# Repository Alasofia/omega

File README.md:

# Omega

Hot swap

Solder

Omega4

The omega is a hot swap 30%(30 or 29 keys depending on the layout you choose) inspired by the [Zlant](https://www.reddit.com/r/MechanicalKeyboards/search?q=zlant&restrict_sr=1) and the [Alpha 28](https://geekhack.org/index.php?topic=99040.0) keyboards.  
The omeaga4 adds a 4th with a few options to make this more than a novelty piece.

The plate files, stls for 3D printing, and STEP files can be found in the [docs](./docs) folder.  
There are also gerbers already generated in the gerber folders.

This version was modified by Alas for LuTang.
The spacebar options were replaced with 2x2u.

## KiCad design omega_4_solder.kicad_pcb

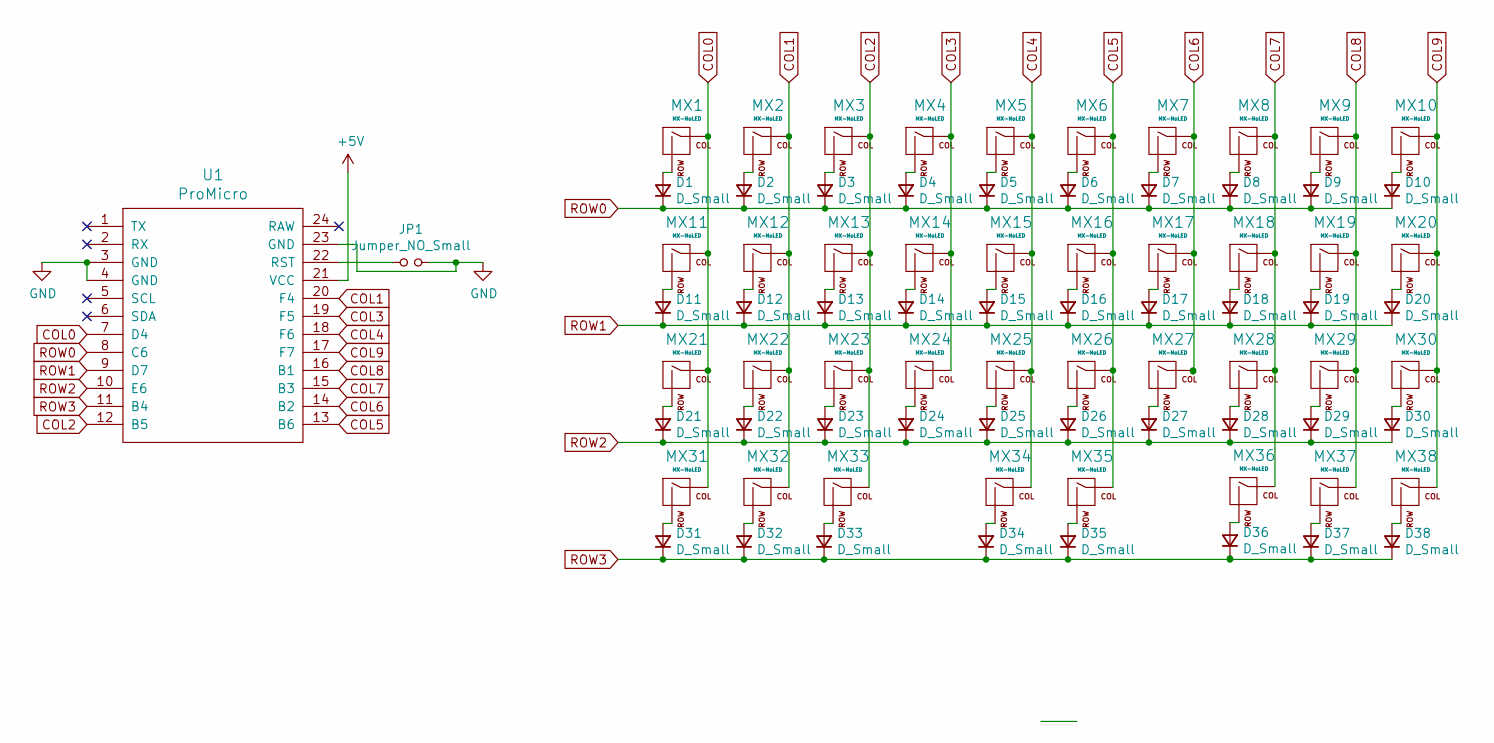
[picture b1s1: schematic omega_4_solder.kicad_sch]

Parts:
D1, D2, D3, D4, D5, D6, D7, D8, D9, D10, D11, D12, D13, D14, D15, D16, D17, D18, D19, D20, D21, D22, D23, D24, D25, D26, D27, D28, D29, D30, D31, D32, D33, D34, D35, D36, D37, D38: D_Small; Diode-Hybrid-Back
JP1: Jumper_NO_Small; Jumper-UserFriendly-Small
MX1, MX2, MX3, MX4, MX5, MX6, MX7, MX8, MX9, MX10, MX11, MX12, MX13, MX14, MX15, MX16, MX17, MX18, MX19, MX20, MX21, MX22, MX23, MX24, MX25, MX26, MX27, MX28, MX29, MX30, MX31, MX32, MX33, MX36, MX37, MX38: MX-NoLED; MXOnly-1U-NoLED
MX34, MX35: MX-NoLED; MXOnly-2U-ReversedStabilizers-NoLED
U1: ProMicro

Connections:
+5V: U1.21 (VCC)
COL0: MX1.1 (COL), MX11.1 (COL), MX21.1 (COL), MX31.1 (COL), U1.7 (D4)
COL1: MX2.1 (COL), MX12.1 (COL), MX22.1 (COL), MX32.1 (COL), U1.20 (F4)
COL2: MX3.1 (COL), MX13.1 (COL), MX23.1 (COL), U1.12 (B5)
COL3: MX4.1 (COL), MX14.1 (COL), MX24.1 (COL), U1.19 (F5)
COL4: MX5.1 (COL), MX15.1 (COL), MX25.1 (COL), U1.18 (F6)
COL5: MX6.1 (COL), MX16.1 (COL), MX26.1 (COL), MX35.1 (COL), U1.13 (B6)
COL6: MX7.1 (COL), MX17.1 (COL), MX27.1 (COL), U1.14 (B2)
COL7: MX8.1 (COL), MX18.1 (COL), MX28.1 (COL), MX36.1 (COL), U1.15 (B3)
COL8: MX9.1 (COL), MX19.1 (COL), MX29.1 (COL), MX37.1 (COL), U1.16 (B1)
COL9: MX10.1 (COL), MX20.1 (COL), MX30.1 (COL), MX38.1 (COL), U1.17 (F7)
GND: JP1.2, U1.3 (GND), U1.4 (GND), U1.23 (GND)
unnamed: D1.2 (A), MX1.2 (ROW)
unnamed: D2.2 (A), MX2.2 (ROW)
unnamed: D3.2 (A), MX3.2 (ROW)
unnamed: D4.2 (A), MX4.2 (ROW)
unnamed: D5.2 (A), MX5.2 (ROW)
unnamed: D6.2 (A), MX6.2 (ROW)
unnamed: D7.2 (A), MX7.2 (ROW)
unnamed: D8.2 (A), MX8.2 (ROW)
unnamed: D9.2 (A), MX9.2 (ROW)
unnamed: D10.2 (A), MX10.2 (ROW)
unnamed: D11.2 (A), MX11.2 (ROW)
unnamed: D12.2 (A), MX12.2 (ROW)
unnamed: D13.2 (A), MX13.2 (ROW)
unnamed: D14.2 (A), MX14.2 (ROW)
unnamed: D15.2 (A), MX15.2 (ROW)
unnamed: D16.2 (A), MX16.2 (ROW)
unnamed: D17.2 (A), MX17.2 (ROW)
unnamed: D18.2 (A), MX18.2 (ROW)
unnamed: D19.2 (A), MX19.2 (ROW)
unnamed: D20.2 (A), MX20.2 (ROW)
unnamed: D21.2 (A), MX21.2 (ROW)
unnamed: D22.2 (A), MX22.2 (ROW)
unnamed: D23.2 (A), MX23.2 (ROW)
unnamed: D24.2 (A), MX24.2 (ROW)
unnamed: D25.2 (A), MX25.2 (ROW)
unnamed: D26.2 (A), MX26.2 (ROW)
unnamed: D27.2 (A), MX27.2 (ROW)
unnamed: D28.2 (A), MX28.2 (ROW)
unnamed: D29.2 (A), MX29.2 (ROW)
unnamed: D30.2 (A), MX30.2 (ROW)
unnamed: D31.2 (A), MX31.2 (ROW)
unnamed: D32.2 (A), MX32.2 (ROW)
unnamed: D33.2 (A), MX33.2 (ROW)
unnamed: D34.2 (A), MX34.2 (ROW)
unnamed: D35.2 (A), MX35.2 (ROW)
unnamed: D36.2 (A), MX36.2 (ROW)
unnamed: D37.2 (A), MX37.2 (ROW)
unnamed: JP1.1, U1.22 (RST)
unnamed: D38.2 (A), MX38.2 (ROW)
ROW0: D1.1 (K), D2.1 (K), D3.1 (K), D4.1 (K), D5.1 (K), D6.1 (K), D7.1 (K), D8.1 (K), D9.1 (K), D10.1 (K), U1.8 (C6)
ROW1: D11.1 (K), D12.1 (K), D13.1 (K), D14.1 (K), D15.1 (K), D16.1 (K), D17.1 (K), D18.1 (K), D19.1 (K), D20.1 (K), U1.9 (D7)
ROW2: D21.1 (K), D22.1 (K), D23.1 (K), D24.1 (K), D25.1 (K), D26.1 (K), D27.1 (K), D28.1 (K), D29.1 (K), D30.1 (K), U1.10 (E6)
ROW3: D31.1 (K), D32.1 (K), D33.1 (K), D34.1 (K), D35.1 (K), D36.1 (K), D37.1 (K), D38.1 (K), U1.11 (B4)

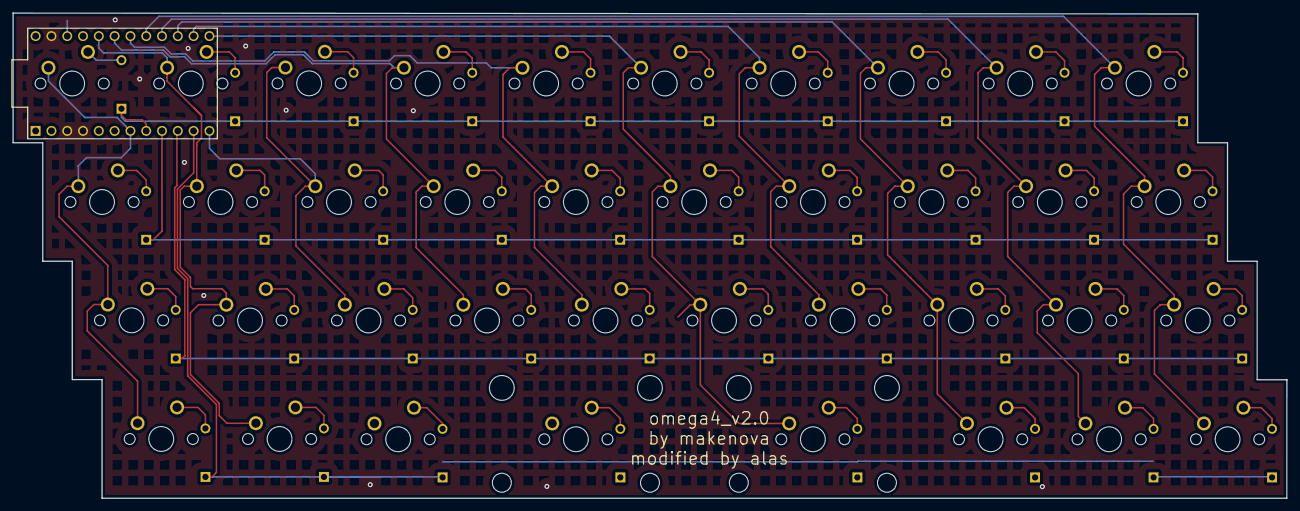
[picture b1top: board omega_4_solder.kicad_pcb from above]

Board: 2 copper layers, 204.8 x 78.0 mm, 78 parts (1 on the bottom side), 54 nets.

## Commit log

2022-12-03 Modified for LuTang
    2x2u instead of big bar
2022-12-10 firmware
